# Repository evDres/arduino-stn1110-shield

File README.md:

# Arduino STN1110 CAN shield

@todo

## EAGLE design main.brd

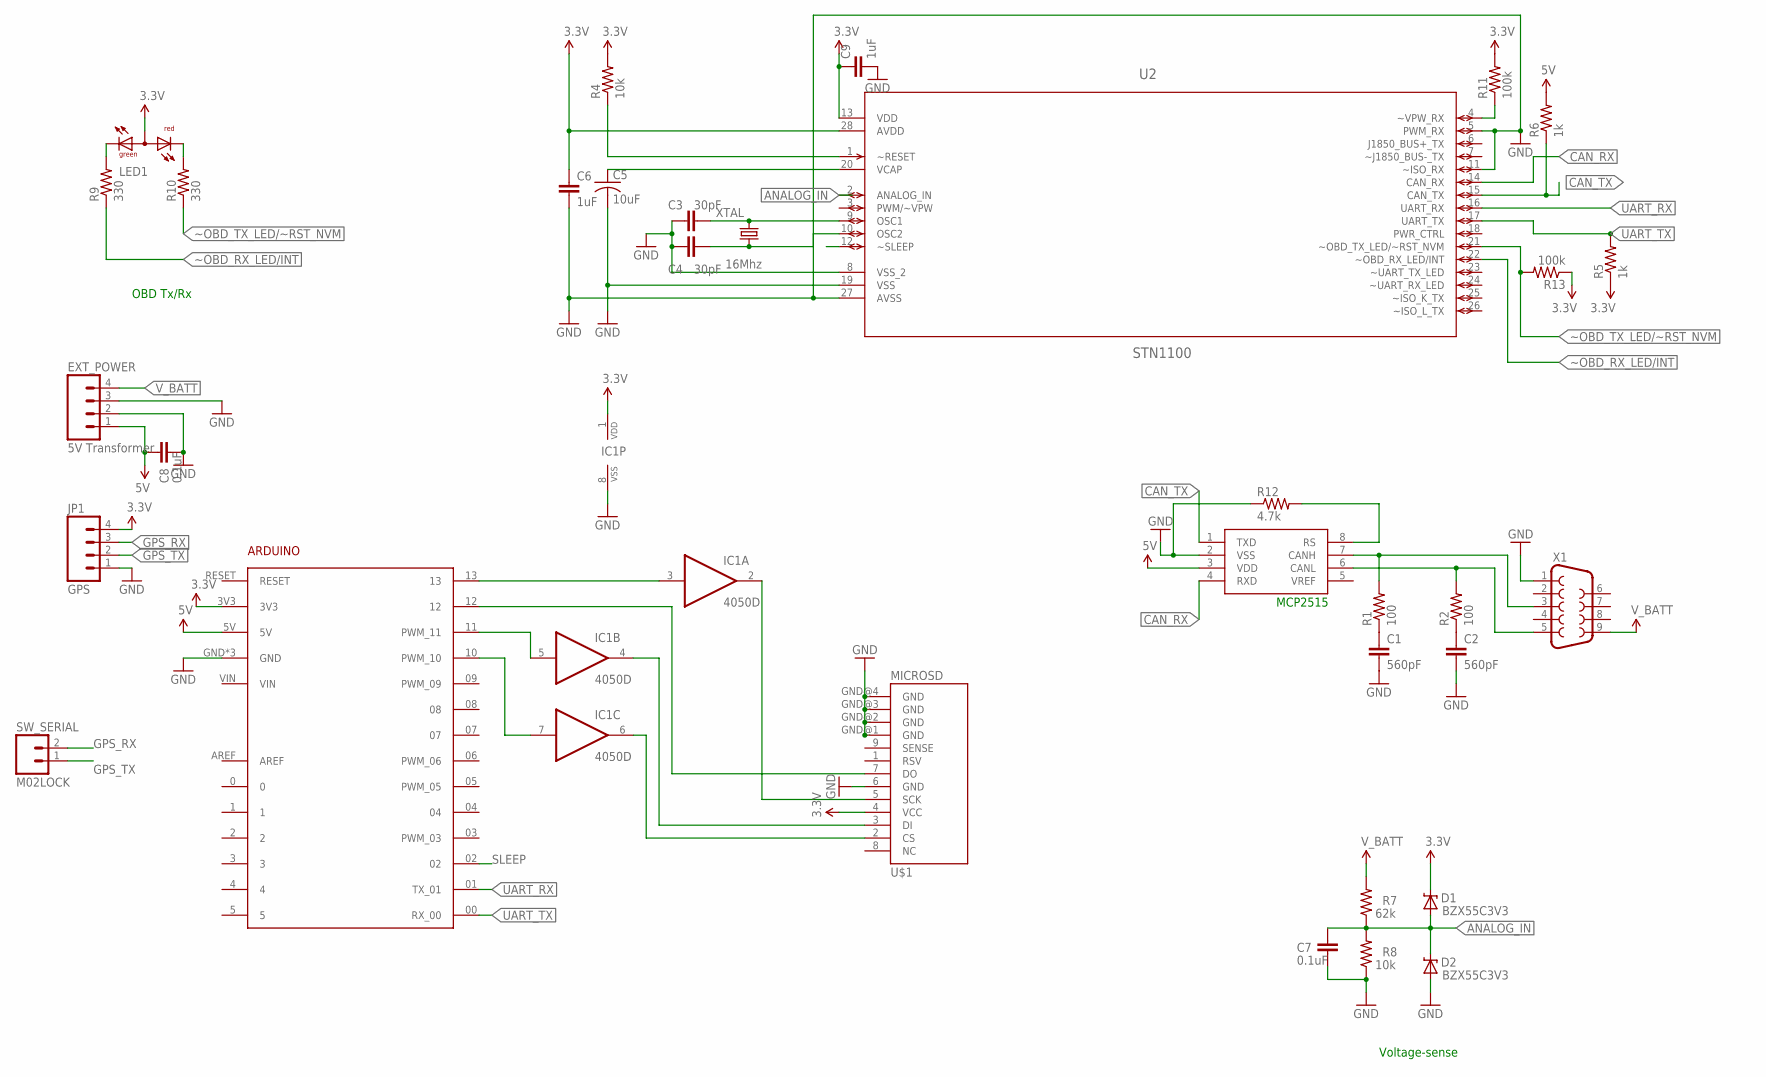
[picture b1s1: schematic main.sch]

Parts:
ARDUINO1: ARDUINO
C1, C2: 560pF; C025-024X044
C3, C4: 30pF; C2.5-2
C5: 10uF; C025-024X044
C6, C9: 1uF; C2.5-2
C7, C8: 0.1uF; C2.5-2
D1, D2: BZX55C3V3; DIODE-ZENER
EXT_POWER: 5V Transformer; 1X04_LOCK
IC1: 4050D; SO16
JP1: GPS; 1X04_LOCK
LED1: OBD RX/TX; DUOLED-A-3MM
R1, R2: 100; 0204/7
R4, R8: 10k; 0204/7
R5, R6: 1k; 0204/7
R7: 62k; 0204/7
R9, R10: 330; 0204/7
R11, R13: 100k; 0204/7
R12: 4.7k; 0204/7
SW_SERIAL: M02LOCK; 1X02_LOCK
U1: MCP2551; SOCKET-08
U2: STN1100; SOCKET-28-3
U$1: MICROSD; MICROSD_PP
X1: DB9MALE; DB9_MALE
XTAL: 16Mhz; HC49U-V

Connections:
3.3V: ARDUINO1.3V3, C9.1, D1.P$1 (C), IC1.1 (VDD), JP1.4, LED1.2 (A), R4.2, R5.1, R11.2, R13.1, U2.13 (VDD), U$1.4 (VCC)
5V: ARDUINO1.5V, C8.1, EXT_POWER.1, R6.2, U1.3 (VDD)
ANALOG_IN: C7.1, D1.P$2 (A), D2.P$1 (C), R7.1, R8.2, U2.2 (ANALOG_IN)
CAN_RX: U1.4 (RXD), U2.14 (CAN_RX)
CAN_TX: R6.1, U1.1 (TXD), U2.15 (CAN_TX)
GND: ARDUINO1.GND, ARDUINO1.GND2 (GND), ARDUINO1.GND3 (GND), C1.2, C2.2, C3.1, C4.1, C5.2, C6.2, C7.2, C8.2, C9.2, D2.P$2 (A), EXT_POWER.2, EXT_POWER.3, IC1.8 (VSS), JP1.1, R8.1, R12.1, U1.2 (VSS), U2.5 (PWM_RX), U2.8 (VSS_2), U2.11 (~ISO_RX), U2.19 (VSS), U2.27 (AVSS), U$1.6 (GND), U$1.GND@1 (GND), U$1.GND@2 (GND), U$1.GND@3 (GND), U$1.GND@4 (GND), X1.1
GPS_RX: JP1.3, SW_SERIAL.2
GPS_TX: JP1.2, SW_SERIAL.1
unnamed: R1.2, U1.7 (CANH), X1.3
unnamed: R2.2, U1.6 (CANL), X1.5
unnamed: C1.1, R1.1
unnamed: C2.1, R2.1
unnamed: C3.2, U2.9 (OSC1), XTAL.2
unnamed: C4.2, U2.10 (OSC2), XTAL.1
unnamed: C5.1, U2.20 (VCAP)
unnamed: R4.1, U2.1 (~RESET)
unnamed: C6.1, U2.28 (AVDD)
unnamed: LED1.1 (CG), R9.2
unnamed: LED1.3 (CR), R10.2
unnamed: R11.1, U2.4 (~VPW_RX)
unnamed: IC1.4 (O), U$1.3 (DI)
unnamed: R12.2, U1.8 (RS)
unnamed: IC1.6 (O), U$1.2 (CS)
unnamed: ARDUINO1.13, IC1.3 (I)
unnamed: IC1.2 (O), U$1.5 (SCK)
unnamed: ARDUINO1.10 (PWM_10), IC1.7 (I)
unnamed: ARDUINO1.12, U$1.7 (DO)
unnamed: ARDUINO1.11 (PWM_11), IC1.5 (I)
SLEEP: ARDUINO1.02, U2.12 (~SLEEP)
UART_RX: ARDUINO1.01 (TX_01), U2.16 (UART_RX)
UART_TX: ARDUINO1.00 (RX_00), R5.2, U2.17 (UART_TX)
V_BATT: EXT_POWER.4, R7.2, X1.9
~OBD_RX_LED/INT: R9.1, U2.22 (~OBD_RX_LED/INT)
~OBD_TX_LED/~RST_NVM: R10.1, R13.2, U2.21 (~OBD_TX_LED/~RST_NVM)

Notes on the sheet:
MCP2515
OBD Tx/Rx
Voltage-sense

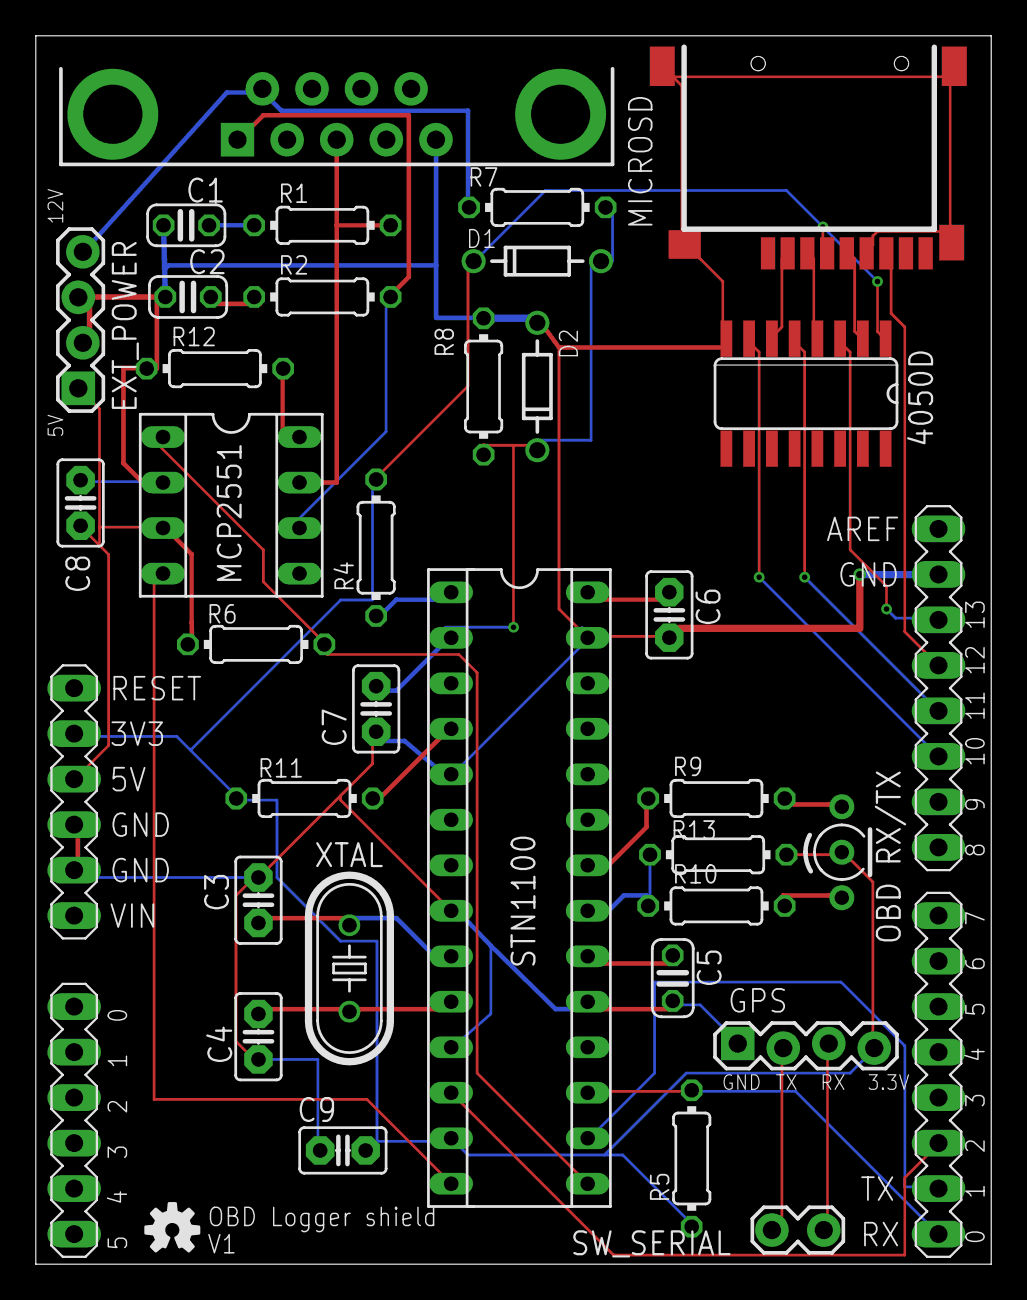
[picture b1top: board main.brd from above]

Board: 4 copper layers, 53.3 x 68.6 mm, 35 parts (0 on the bottom side), 34 nets.

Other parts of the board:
U$2: OSHW-LOGO-S

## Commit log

2014-01-13 Initial (late) commit
2014-01-14 Added some space and better routing
2014-01-15 Improved routing, added micro-sd slot
2014-01-20 Wired the SD card and level shifter
2014-01-20 Better layout...
2014-01-20 Finished wiring, added external v-supply
2014-01-21 fix missing board
2014-01-23 Reduced footprint, fixed DB9 connector
2014-01-25 Resized and ready for printing
2014-01-27 Review phase 1
2014-01-30 Ready to print\!
2014-03-27 Fixed errors on UART tx/rx

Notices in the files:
parts and their libraries:
SparkFun-FreqCtrl: Licensing: CC v3.0 Share-Alike You are welcome to use this library for commercial purposes.
